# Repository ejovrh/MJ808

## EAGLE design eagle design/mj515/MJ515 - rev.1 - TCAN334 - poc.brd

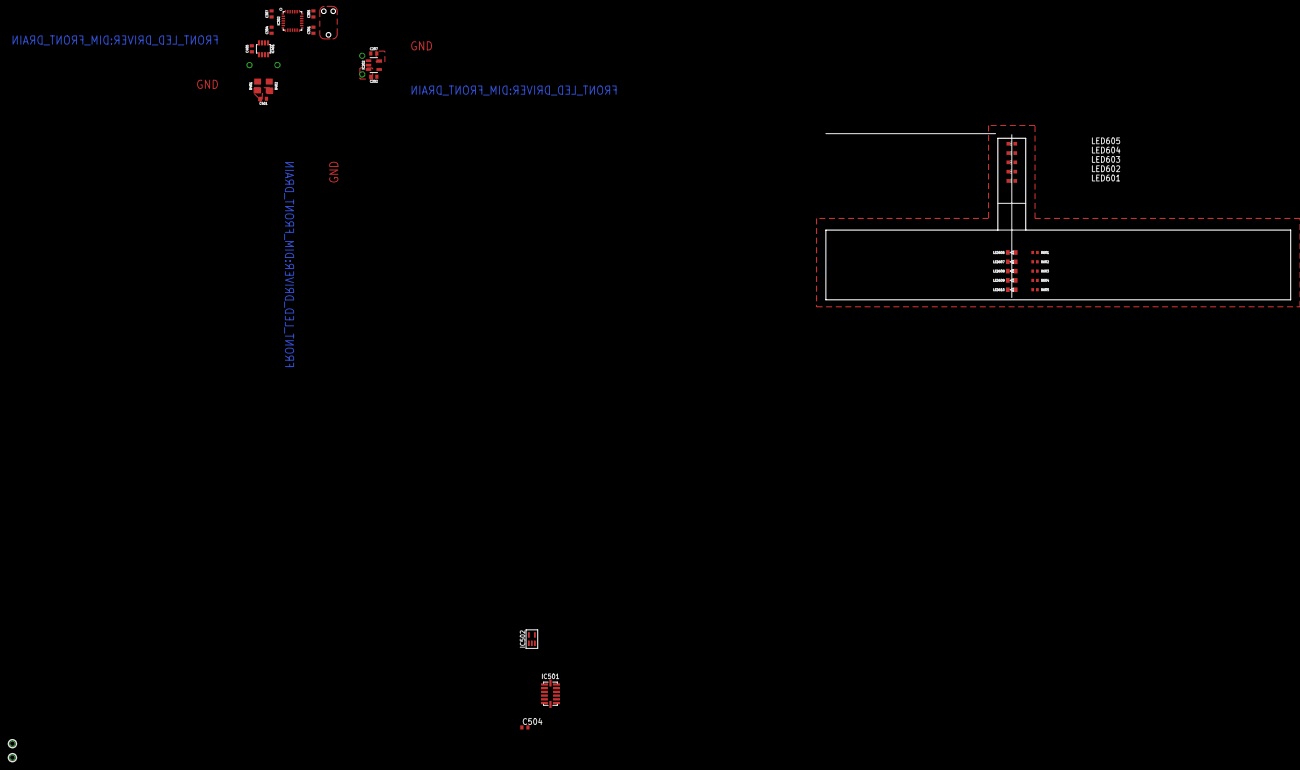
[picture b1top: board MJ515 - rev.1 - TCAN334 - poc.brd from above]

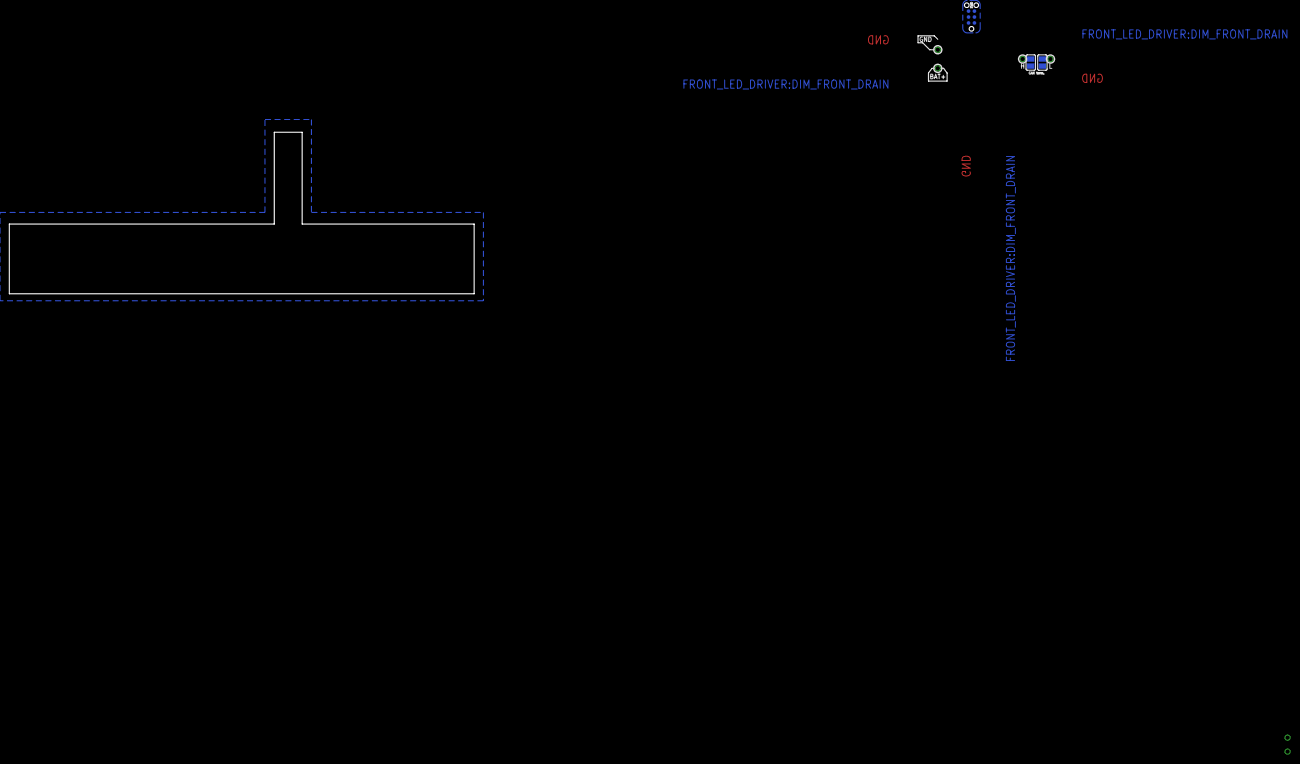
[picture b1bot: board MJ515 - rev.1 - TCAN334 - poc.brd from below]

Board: 2 copper layers, 100.0 x 34.8 mm, 40 parts (7 on the bottom side), 25 nets, no tracks yet.

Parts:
C202, C207, C304: 1uF / 10V; C0402
C301, C305, C307, C405: 0.1uF / 10V; C0402
C401: 47nF / 10V; C0402
C504: 0.1u / 16V; C0402
IC202: LDK320AM33R; SOT-23-5L
IC302: STM32F042G6U6; UFQFPN-28
IC401: TCAN334; SOT23-8
IC501: ADXL345; LGA14
IC502: 74HCT1G32GW; SOT353/5
LED601, LED602, LED603, LED604, LED605: CHIP-LED0603
LED606, LED607, LED608, LED609, LED610: 0603
R401, R402: 60R, 0.5W; R0805
R601, R602, R603, R604, R605: 10k; R0402
SJ401: CAN H term.; SJ
SJ402: CAN L term.; SJ
SWD1: TC2030-NL
TP1: LiIon + Terminal; TH-0.9
TP2: LiIon - Terminal; TH-0.9
TP3, TP5: CAN high; TH-0.9
TP4, TP6: CAN low; TH-0.9

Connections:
3V3: C207.2, C301.2, C304.2, C305.2, C405.1, C504.1, IC202.OUT, IC302.5_VDDA, IC302.17_VDD, IC302.18_VDDIO2, IC401.P$3, IC501.VCC, IC501.VDD, IC502.VCC, LED606.C, LED607.C, LED608.C, LED609.C, LED610.C, SWD1.1_TVCC
!STBY!: IC302.23_PA15, IC401.P$8
ACCELEROMETER:ADXL345SDA: IC501.SDA, IC502.Y
ADXL345_INT1: IC302.6_PA0, IC501.INT1
BAT+: C202.1, IC202.EN, IC202.IN, TP1.P$1
BIT1: IC302.24_PB3, LED607.E, R602.2
BIT2: IC302.25_PB4, LED608.E, R603.2
BIT3: IC302.26_PB5, LED609.E, R604.2
BIT4: IC302.27_PB6, LED610.E, R605.2
CAN_H: IC401.P$7, SJ401.1, TP3.P$1, TP5.P$1
CAN_INFRA:H: R402.2, SJ401.2
CAN_INFRA:L: R401.1, SJ402.2
CAN_INFRA:SPLIT: C401.1, R401.2, R402.1
CAN_L: IC401.P$6, SJ402.1, TP4.P$1, TP6.P$1
CAN_RX: IC302.19_PA9-[PA11], IC401.P$4
CAN_TX: IC302.20_PA10-[PA12], IC401.P$1
CLK: IC302.11_PA5, IC501.SCL
CS: IC302.10_PA4, IC501.!CS!, IC502.A
GND: C202.2, C207.1, C301.1, C304.1, C305.1, C307.1, C401.2, C405.2, C504.2, IC202.GND, IC302.16_VSS, IC401.P$2, IC501.GND1, IC501.GND2, IC501.GND3, IC502.GND, R601.1, R602.1, R603.1, R604.1, R605.1, SWD1.5_GND, TP2.P$1
IDX: IC302.7_PA1, LED606.E, R601.2
MISO: IC302.12_PA6, IC501.SDO
MOSI: IC302.13_PA7, IC502.B
SYS_NRST: C307.2, IC302.4_NRST, SWD1.3_T_NRST
SYS_SWCLK: IC302.22_PA14, SWD1.4_T_SWCLK
SYS_SWDIO: IC302.21_PA13, SWD1.2_T_SWDIO

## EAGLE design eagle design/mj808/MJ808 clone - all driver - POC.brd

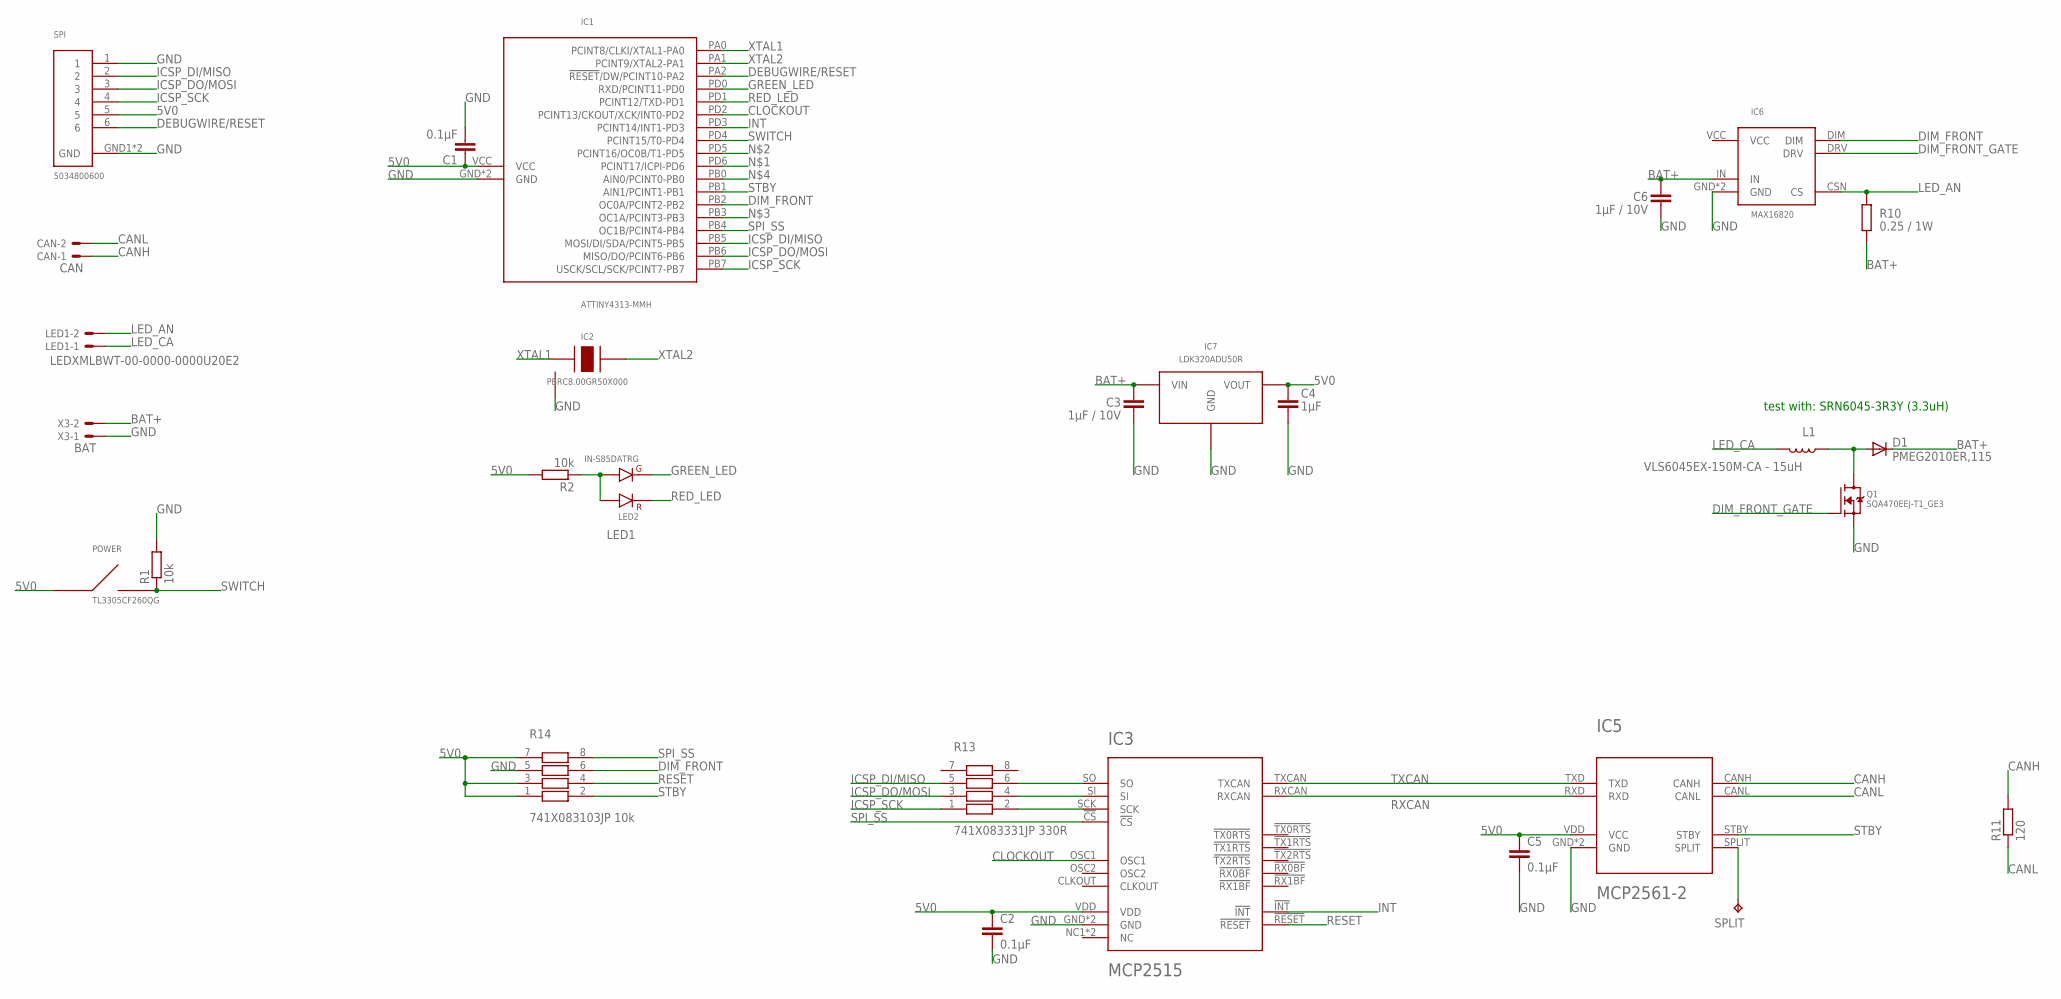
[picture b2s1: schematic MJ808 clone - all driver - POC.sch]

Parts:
C1, C2, C5: 0.1μF; C0402
C3, C6: 1μF / 10V; C0402
C4: 1μF; C0402
CAN: CAN; 22-23-2021
D1: PMEG2010ER,115; SOD123
IC1: ATTINY4313-MMH; VQFN-20
IC2: PBRC8.00GR50X000; SMT
IC3: MCP2515; QFN20
IC5: MCP2561-2; DFN10
IC6: MAX16820; TDFN-6-EP
IC7: LDK320ADU50R; SOT-89
L1: VLS6045EX-150M-CA - 15uH; SRN6045
LED1: LEDXMLBWT-00-0000-0000U20E2; 22-23-2021
LED2: IN-S85DATRG; SMD
POWER: TL3305CF260QG; SMD
Q1: SQA470EEJ-T1_GE3; SC-70-6
R1, R2: 10k; R0402
R10: 0.25 / 1W; R1210
R11: 120; R0805
R13: 741X083331JP 330R; 0402
R14: 741X083103JP 10k; 0402
SPI: 5034800600; SMT
SPLIT: TPB2,54; B2,54
X3: BAT; 22-23-2021

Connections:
5V0: C1.1, C2.1, C4.2, C5.1, IC1.VCC, IC3.VDD, IC5.VDD (VCC), IC7.VOUT, POWER.1, POWER.2, R2.2, R14.1, R14.3, R14.7, SPI.5
BAT+: C3.1, C6.1, D1.C, IC6.IN, IC7.VIN, R10.2, X3.2
CANH: CAN.1, IC5.CANH, R11.2
CANL: CAN.2, IC5.CANL, R11.1
CLOCKOUT: IC1.PD2 (PCINT13/CKOUT/XCK/INT0-PD2), IC3.OSC1
DEBUGWIRE/RESET: IC1.PA2 (!RESET!/DW/PCINT10-PA2), SPI.6
DIM_BRAKE_DRAIN: D1.A, L1.1, Q1.D
DIM_FRONT: IC1.PB2 (OC0A/PCINT2-PB2), IC6.DIM, R14.6
DIM_FRONT_GATE: IC6.DRV, Q1.G
GND: C1.2, C2.2, C3.2, C4.1, C5.2, C6.2, IC1.GND, IC1.GND1 (GND), IC2.GND, IC3.GND, IC3.GND6 (GND), IC5.GND, IC5.VSS (GND), IC6.GND, IC6.GND1 (GND), IC7.GND, Q1.S, R1.2, R14.5, SPI.1, SPI.GND1 (GND), SPI.GND2 (GND), X3.1
GREEN_LED: IC1.PD0 (RXD/PCINT11-PD0), LED2.3
ICSP_DI/MISO: IC1.PB5 (MOSI/DI/SDA/PCINT5-PB5), R13.5, SPI.2
ICSP_DO/MOSI: IC1.PB6 (MISO/DO/PCINT6-PB6), R13.3, SPI.3
ICSP_SCK: IC1.PB7 (USCK/SCL/SCK/PCINT7-PB7), R13.1, SPI.4
INT: IC1.PD3 (PCINT14/INT1-PD3), IC3.!INT!
LED1: LED2.1, LED2.4, R2.1
LED_AN: IC6.CSN (CS), LED1.2, R10.1
LED_CA: L1.2, LED1.1
RED_LED: IC1.PD1 (PCINT12/TXD-PD1), LED2.2
RESET: IC3.!RESET!, R14.4
RXCAN: IC3.RXCAN, IC5.RXD
SPI_MISO: IC3.SO, R13.6
SPI_MOSI: IC3.SI, R13.4
SPI_SCK: IC3.SCK, R13.2
SPI_SS: IC1.PB4 (OC1B/PCINT4-PB4), IC3.!CS!, R14.8
SPLIT: IC5.SPLIT, SPLIT.TP
STBY: IC1.PB1 (AIN1/PCINT1-PB1), IC5.STBY, R14.2
SWITCH: IC1.PD4 (PCINT15/T0-PD4), POWER.3, POWER.4, R1.1
TXCAN: IC3.TXCAN, IC5.TXD
VCC: IC6.VCC
XTAL1: IC1.PA0 (PCINT8/CLKI/XTAL1-PA0), IC2.XTAL1
XTAL2: IC1.PA1 (PCINT9/XTAL2-PA1), IC2.XTAL2

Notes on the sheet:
test with: SRN6045-3R3Y (3.3uH)

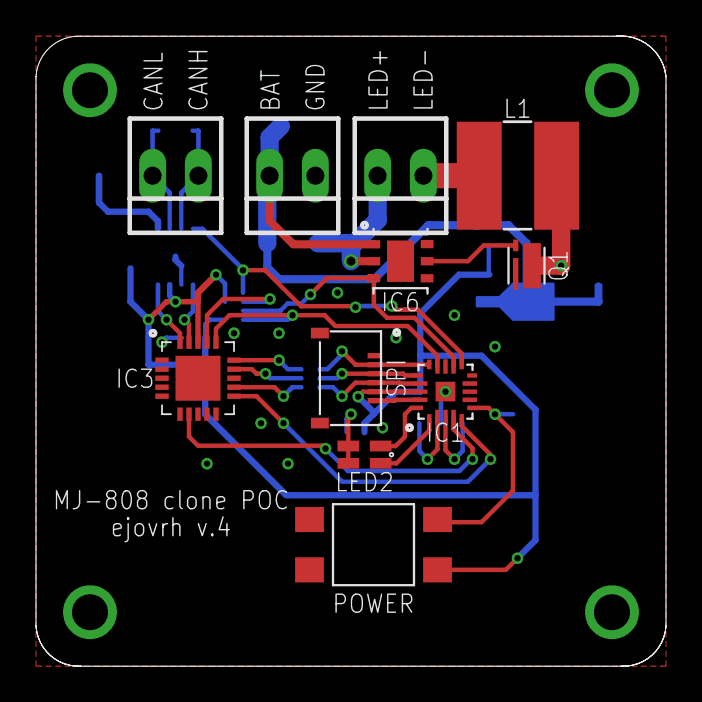
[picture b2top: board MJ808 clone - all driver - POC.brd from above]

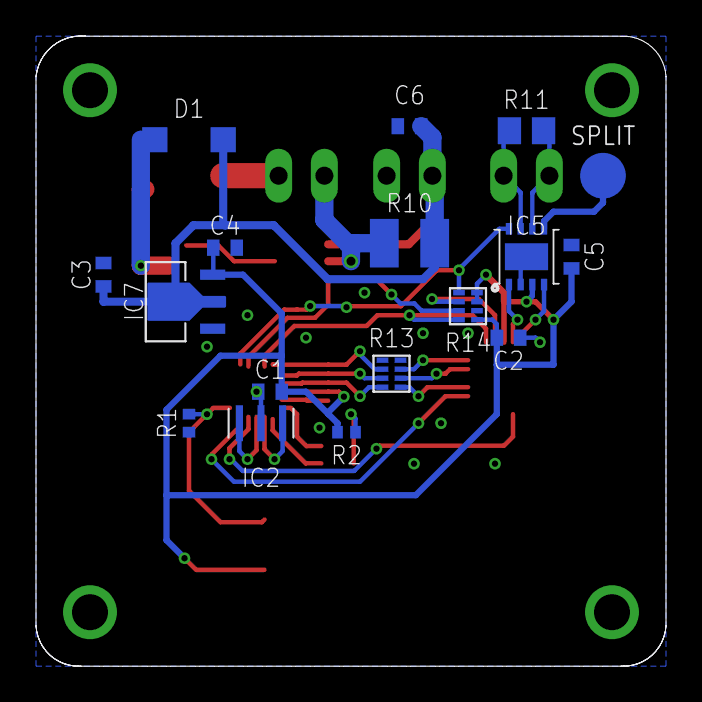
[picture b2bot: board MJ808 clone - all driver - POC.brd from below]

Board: 2 copper layers, 35.0 x 35.0 mm, 28 parts (17 on the bottom side), 31 nets.

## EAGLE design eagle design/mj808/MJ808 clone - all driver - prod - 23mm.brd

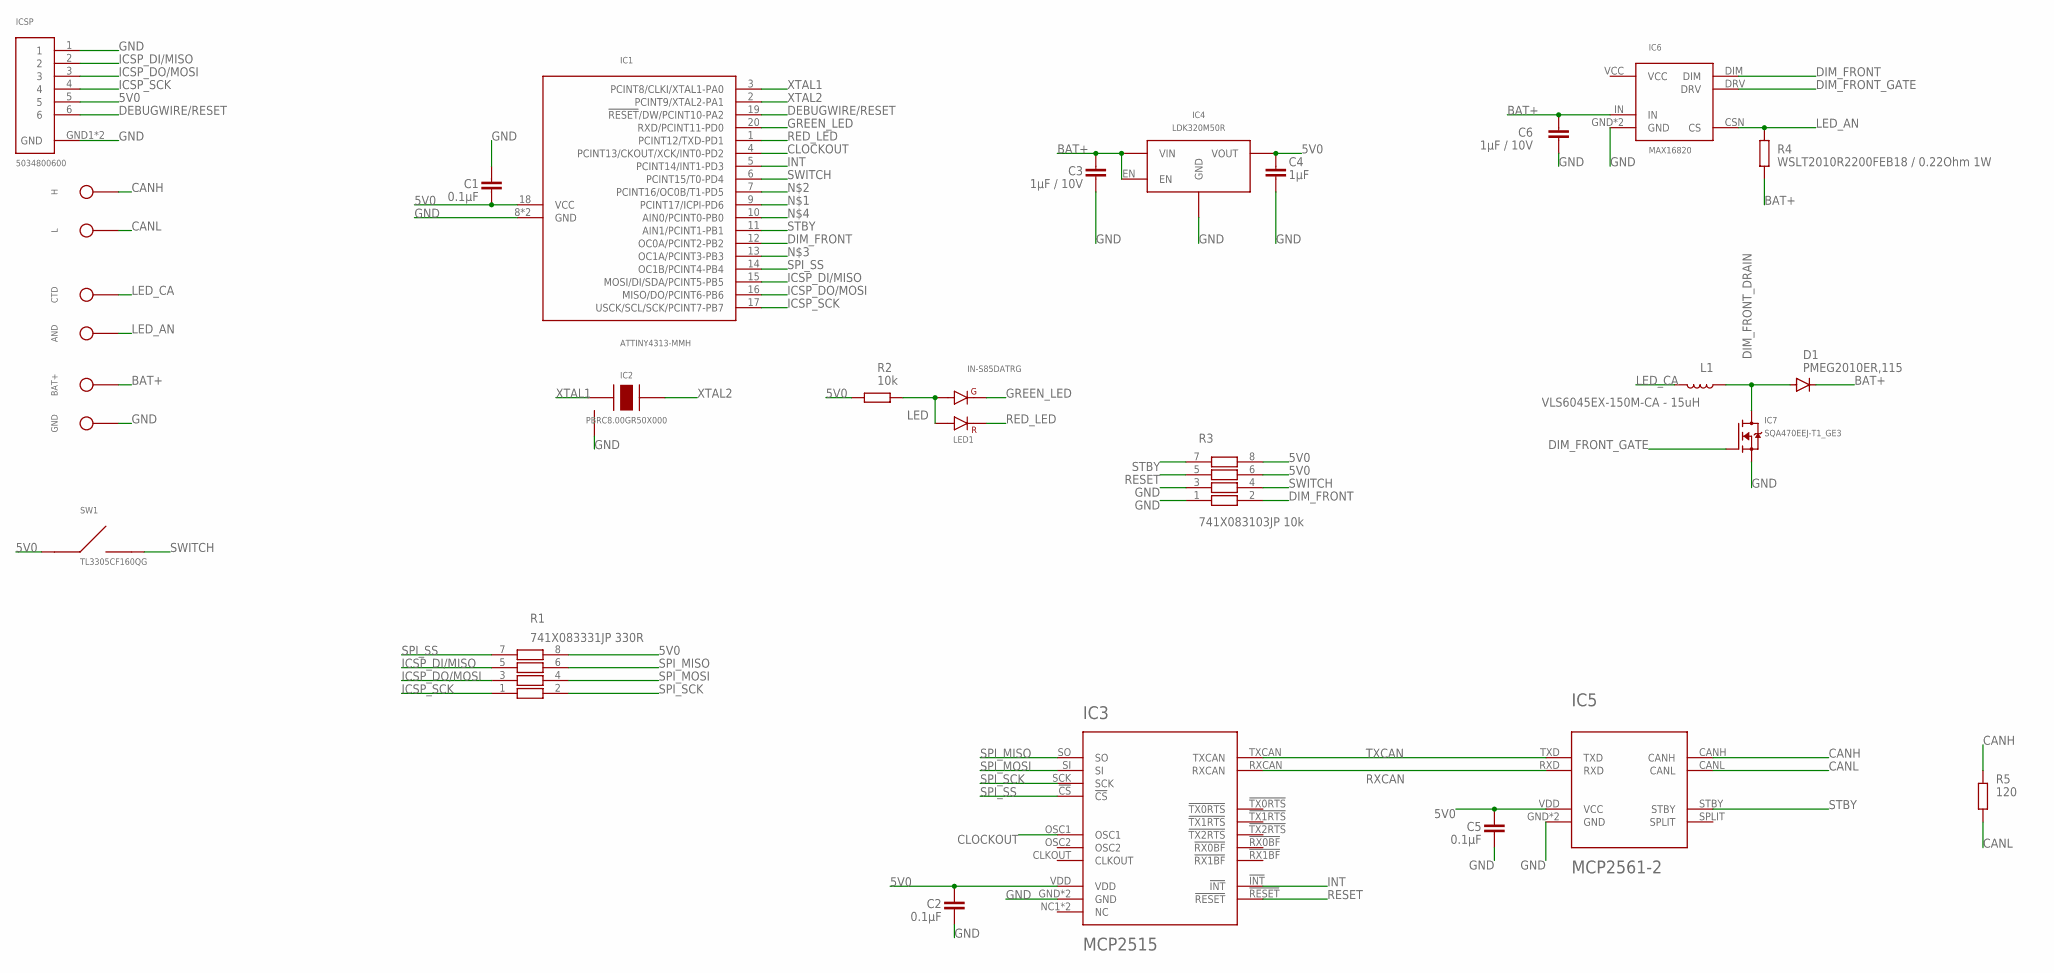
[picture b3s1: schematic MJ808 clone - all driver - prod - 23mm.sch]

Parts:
AND: LED anode; TH-1.2MM
BAT+: LiIon + Terminal; TH-1.2MM
C1, C2, C5: 0.1μF; C0402
C3, C6: 1μF / 10V; C0402
C4: 1μF; C0402
CTD: LED cathode; TH-1.2MM
D1: PMEG2010ER,115; SOD123
GND: LiIon - Terminal; TH-1.2MM
H: CAN high; TH-1.2MM
IC1: ATTINY4313-MMH; VQFN-20
IC2: PBRC8.00GR50X000; SMT
IC3: MCP2515; QFN20
IC4: LDK320M50R; SOT-23-5L
IC5: MCP2561-2; DFN10
IC6: MAX16820; TDFN-6-EP
IC7: SQA470EEJ-T1_GE3; SC-70-6
ICSP: 5034800600; SMT
L: CAN low; TH-1.2MM
L1: VLS6045EX-150M-CA - 15uH; SRN6045
LED1: IN-S85DATRG; SMD
R1: 741X083331JP 330R; 0402-4R
R2: 10k; R0402
R3: 741X083103JP 10k; 0402-4R
R4: WSLT2010R2200FEB18 / 0.22Ohm 1W; R2010
R5: 120; R0805
SW1: TL3305CF160QG; SMD

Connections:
5V0: C1.1, C2.1, C4.2, C5.1, IC1.18 (VCC), IC3.VDD, IC4.OUT (VOUT), IC5.VDD (VCC), ICSP.5, R1.8, R2.2, R3.6, R3.8, SW1.1, SW1.2
BAT+: BAT+.TP$1, C3.1, C6.1, D1.C, IC4.EN, IC4.IN (VIN), IC6.IN, R4.2
CANH: H.TP$1, IC5.CANH, R5.2
CANL: IC5.CANL, L.TP$1, R5.1
CLOCKOUT: IC1.4 (PCINT13/CKOUT/XCK/INT0-PD2), IC3.OSC1
DEBUGWIRE/RESET: IC1.19 (!RESET!/DW/PCINT10-PA2), ICSP.6
DIM_FRONT: IC1.12 (OC0A/PCINT2-PB2), IC6.DIM, R3.2
DIM_FRONT_DRAIN: D1.A, IC7.1D (D), IC7.2D (D), IC7.5D (D), IC7.6D (D), IC7.D, L1.1
DIM_FRONT_GATE: IC6.DRV, IC7.3G (G)
GND: C1.2, C2.2, C3.2, C4.1, C5.2, C6.2, GND.TP$1, IC1.8 (GND), IC1.GND, IC2.GND, IC3.GND, IC3.GND6 (GND), IC4.GND, IC5.GND, IC5.VSS (GND), IC6.GND, IC6.GND1 (GND), IC7.4S (S), IC7.S, ICSP.1, ICSP.GND1 (GND), ICSP.GND2 (GND), R3.1, R3.3
GREEN_LED: IC1.20 (RXD/PCINT11-PD0), LED1.3
ICSP_DI/MISO: IC1.15 (MOSI/DI/SDA/PCINT5-PB5), ICSP.2, R1.5
ICSP_DO/MOSI: IC1.16 (MISO/DO/PCINT6-PB6), ICSP.3, R1.3
ICSP_SCK: IC1.17 (USCK/SCL/SCK/PCINT7-PB7), ICSP.4, R1.1
INT: IC1.5 (PCINT14/INT1-PD3), IC3.!INT!
LED: LED1.1, LED1.4, R2.1
LED_AN: AND.TP$1, IC6.CSN (CS), R4.1
LED_CA: CTD.TP$1, L1.2
unnamed: IC1.3 (PCINT8/CLKI/XTAL1-PA0), IC2.XTAL1
unnamed: IC1.2 (PCINT9/XTAL2-PA1), IC2.XTAL2
RED_LED: IC1.1 (PCINT12/TXD-PD1), LED1.2
RESET: IC3.!RESET!, R3.5
RXCAN: IC3.RXCAN, IC5.RXD
SPI_MISO: IC3.SO, R1.6
SPI_MOSI: IC3.SI, R1.4
SPI_SCK: IC3.SCK, R1.2
SPI_SS: IC1.14 (OC1B/PCINT4-PB4), IC3.!CS!, R1.7
STBY: IC1.11 (AIN1/PCINT1-PB1), IC5.STBY, R3.7
SWITCH: IC1.6 (PCINT15/T0-PD4), R3.4, SW1.3, SW1.4
TXCAN: IC3.TXCAN, IC5.TXD
VCC: IC6.VCC

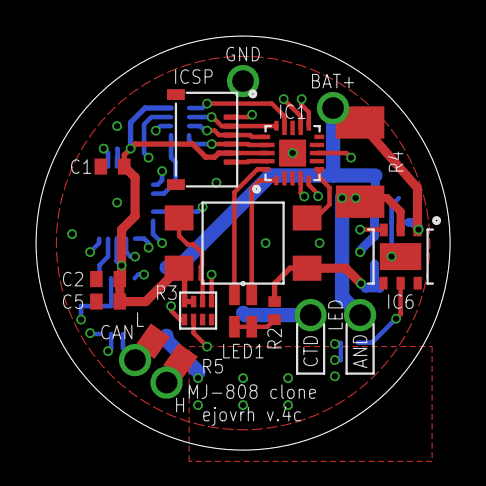
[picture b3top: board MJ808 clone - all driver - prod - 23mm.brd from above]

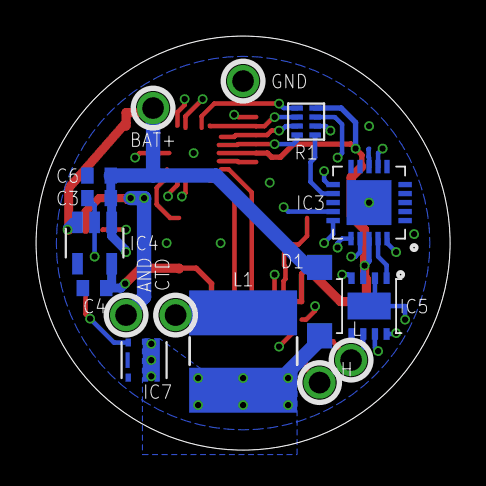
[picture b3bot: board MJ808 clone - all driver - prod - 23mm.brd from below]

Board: 4 copper layers, 23.0 x 23.0 mm, 28 parts (16 on the bottom side), 28 nets.

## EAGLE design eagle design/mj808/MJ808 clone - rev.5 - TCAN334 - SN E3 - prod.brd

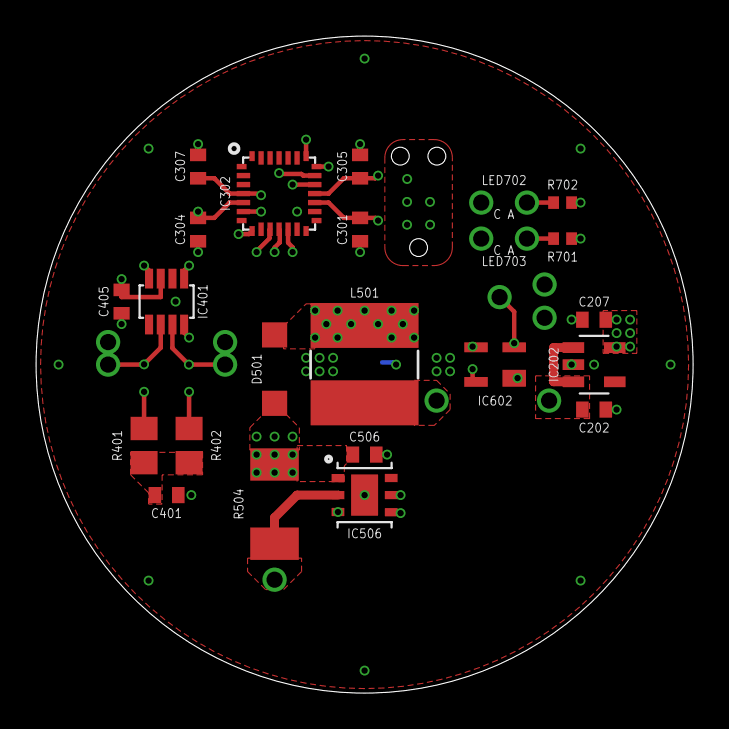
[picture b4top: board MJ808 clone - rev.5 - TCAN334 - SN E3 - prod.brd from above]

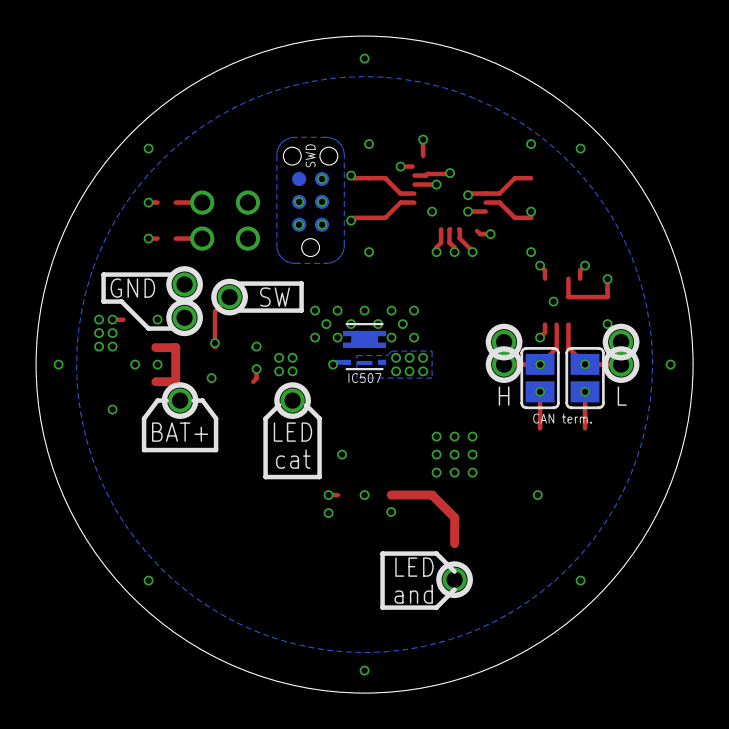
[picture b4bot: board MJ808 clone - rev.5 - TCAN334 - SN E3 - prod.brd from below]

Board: 4 copper layers, 36.5 x 36.5 mm, 37 parts (14 on the bottom side), 25 nets.

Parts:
C202, C207, C304, C506: 1uF / 10V; C0402
C301, C305, C307, C405: 0.1uF / 10V; C0402
C401: 47nF / 10V; C0402
D501: PMEG2010ER,115; SOD123
IC202: LDK320AM33R; SOT-23-5L
IC302: STM32F042G6U6; UFQFPN-28
IC401: TCAN334; SOT23-8
IC506: MAX16820; TDFN-6-EP
IC507: SQA470EEJ-T1_GE3; SC-70-6
IC602: MAX6816EUS+T; 4SOT143
L501: VLS6045EX-150M-CA - 15uH; SRN6045
LED702: WP7113VRVC1C; TH
LED703: LTL2R3TGY3KS; TH
R401, R402: 60R, 0.5W; R0805
R504: 0.18R; R2010
R701, R702: 0R, >120mW; R0402
SJ401: CAN H term.; SJ
SJ402: CAN L term.; SJ
SWD1: TC2030-NL
TP1: LiIon + Terminal; TH-0.9
TP2: LiIon - Terminal; TH-0.9
TP3, TP601, TP602: LED anode; TH-0.9
TP4: LED cathode; TH-0.9
TP5, TP7: CAN high; TH-0.9
TP6, TP8: CAN low; TH-0.9

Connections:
3V3: C207.2, C301.2, C304.2, C305.2, C405.1, IC202.OUT, IC302.5_VDDA, IC302.17_VDD, IC302.18_VDDIO2, IC401.P$3, IC602.4_VCC, R701.1, R702.1, SWD1.1_TVCC
!STBY!: IC302.11_PA5, IC401.P$8
BAT+: C202.1, C506.1, D501.C, IC202.EN, IC202.IN, IC506.IN, R504.2, TP1.P$1
CAN_H: IC401.P$7, SJ401.1, TP5.P$1, TP7.P$1
CAN_INFRA:H: R402.2, SJ401.2
CAN_INFRA:L: R401.1, SJ402.2
CAN_INFRA:SPLIT: C401.1, R401.2, R402.1
CAN_L: IC401.P$6, SJ402.1, TP6.P$1, TP8.P$1
CAN_RX: IC302.19_PA9-[PA11], IC401.P$4
CAN_TX: IC302.20_PA10-[PA12], IC401.P$1
DIM_FRONT: IC302.12_PA6, IC506.DIM
FRONT_LED_DRIVER:DIM_FRONT_DRAIN: D501.A, IC507.1D, IC507.2D, IC507.5D, IC507.6D, IC507.D, L501.1
FRONT_LED_DRIVER:DIM_FRONT_GATE: IC506.DRV, IC507.3G
GND: C202.2, C207.1, C301.1, C304.1, C305.1, C307.1, C401.2, C405.2, C506.2, IC202.GND, IC302.16_VSS, IC401.P$2, IC506.GND, IC506.GND1, IC507.4S, IC507.S, IC602.1_GND, SWD1.5_GND, TP2.P$1, TP602.P$1
GREEN: IC302.10_PA4, LED703.CAT
LED_AN: IC506.CSN, R504.1, TP3.P$1
LED_CA: L501.2, TP4.P$1
PUSHBUTTON:SWITCH_IN: IC602.2_IN, TP601.P$1
RED: IC302.8_PA2, LED702.CAT
SWITCH: IC302.6_PA0, IC602.3_OUT
SYS_NRST: C307.2, IC302.4_NRST, SWD1.3_T_NRST
SYS_SWCLK: IC302.22_PA14, SWD1.4_T_SWCLK
SYS_SWDIO: IC302.21_PA13, SWD1.2_T_SWDIO
USER_LED:GREEN_AND: LED703.AND, R701.2
USER_LED:RED_AND: LED702.AND, R702.2

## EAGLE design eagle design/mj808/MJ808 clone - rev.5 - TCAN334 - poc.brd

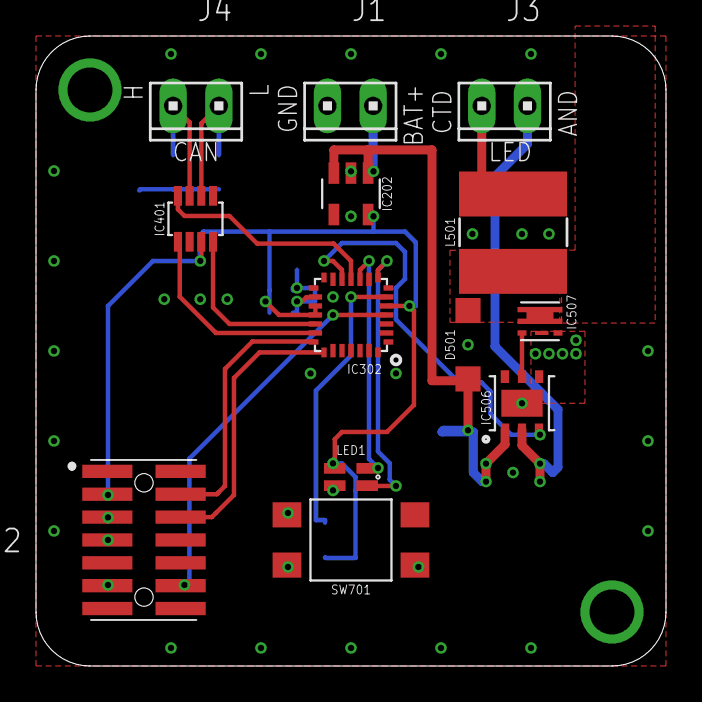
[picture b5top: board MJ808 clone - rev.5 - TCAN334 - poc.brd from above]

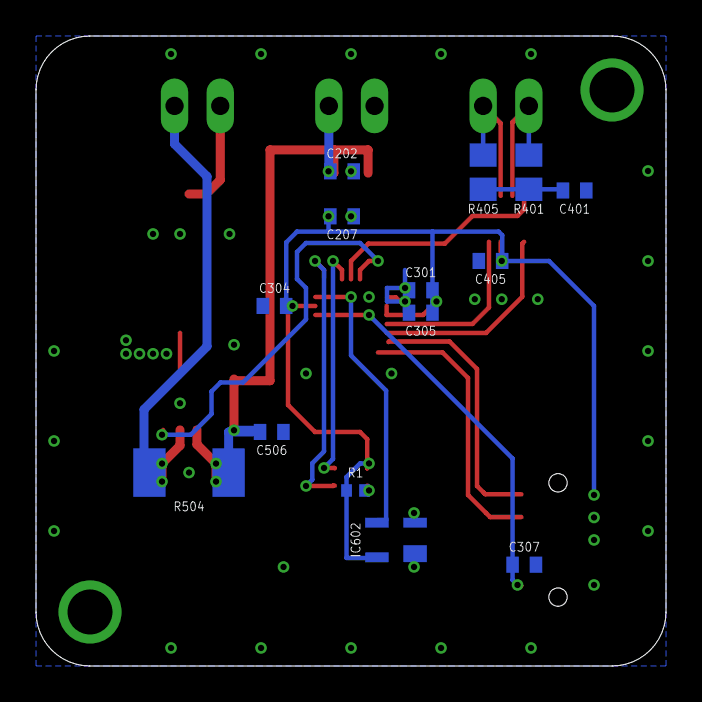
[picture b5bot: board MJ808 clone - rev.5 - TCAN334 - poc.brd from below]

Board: 2 copper layers, 35.0 x 35.0 mm, 27 parts (14 on the bottom side), 22 nets.

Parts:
C202, C207, C304, C506: 1uF / 10V; C0402
C301, C305, C307, C405: 0.1uF / 10V; C0402
C401: 47nF / 10V; C0402
D501: PMEG2010ER,115; SOD123
IC202: LDK320AM33R; SOT-23-5L
IC302: STM32F042G6U6; UFQFPN-28
IC401: TCAN334; SOT23-8
IC506: MAX16820; TDFN-6-EP
IC507: SQA470EEJ-T1_GE3; SC-70-6
IC602: MAX6816EUS+T; 4SOT143
J1: Power Supply; 10X02MTA
J2: FTSH-107-01-L-DV-K-A; FTSH10701LDVKA
J3: LED; 10X02MTA
J4: CAN; 10X02MTA
L501: VLS6045EX-150M-CA - 15uH; SRN6045
LED1: APHBM2012SURKZGKC; SMD
R1: 68R; R0402
R401, R405: 60; R0805
R504: WSLT2010R2200FEB18 / 0.22Ohm 1W; R2010
SW701: TL3305CF160QG; SMD

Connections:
3V3: C207.2, C301.2, C304.2, C305.2, C405.1, IC202.OUT, IC302.5_VDDA, IC302.17_VDD, IC302.18_VDDIO2, IC401.P$3, IC602.4_VCC, J2.3, LED1.4, R1.1
!STBY!: IC302.11_PA5, IC401.P$8
BAT+: C202.1, C506.1, D501.C, IC202.EN, IC202.IN, IC506.IN, J1.2, R504.2
CAN_H: IC401.P$7, J4.1, R401.2
CAN_INFRA:SPLIT: C401.1, R401.1, R405.2
CAN_L: IC401.P$6, J4.2, R405.1
CAN_RX: IC302.19_PA9-[PA11], IC401.P$4
CAN_TX: IC302.20_PA10-[PA12], IC401.P$1
DIM_FRONT: IC302.12_PA6, IC506.DIM
FRONT_LED_DRIVER:DIM_FRONT_DRAIN: D501.A, IC507.1D, IC507.2D, IC507.5D, IC507.6D, IC507.D, L501.1
FRONT_LED_DRIVER:DIM_FRONT_GATE: IC506.DRV, IC507.3G
GND: C202.2, C207.1, C301.1, C304.1, C305.1, C307.1, C401.2, C405.2, C506.2, IC202.GND, IC302.16_VSS, IC401.P$2, IC506.GND, IC506.GND1, IC507.4S, IC507.S, IC602.1_GND, J1.1, J2.5, J2.7, J2.11, SW701.3, SW701.4
GREEN_LED: IC302.10_PA4, LED1.3
LED_AN: IC506.CSN, J3.2, R504.1
LED_CA: J3.1, L501.2
PUSHBUTTON:SWITCH_IN: IC602.2_IN, SW701.1, SW701.2
RED_LED: IC302.8_PA2, LED1.2
SWITCH: IC302.6_PA0, IC602.3_OUT
SYS_NRST: C307.2, IC302.4_NRST, J2.12
SYS_SWCLK: IC302.22_PA14, J2.6
SYS_SWDIO: IC302.21_PA13, J2.4
USER-LED-CTD: LED1.1, R1.2

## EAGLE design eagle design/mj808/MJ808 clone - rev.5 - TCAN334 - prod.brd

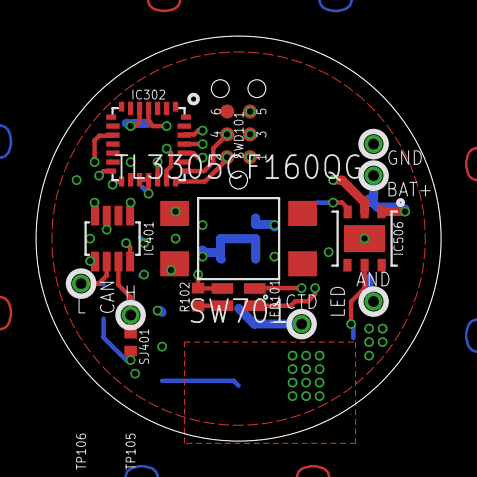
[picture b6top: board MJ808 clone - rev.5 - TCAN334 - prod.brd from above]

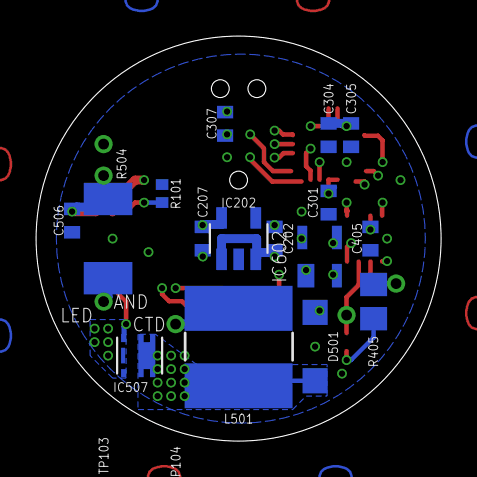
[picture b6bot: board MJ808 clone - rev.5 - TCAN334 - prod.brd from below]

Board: 4 copper layers, 22.5 x 22.5 mm, 30 parts (16 on the bottom side), 23 nets.

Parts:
C202, C506: 1μF / 10V; C0402
C207: 1μF; C0402
C301, C305, C307: 0.1u; C0402
C304: 1u; C0402
C405: 0.1μF; C0402
D501: PMEG2010ER,115; SOD123
IC202: LDK320AM33R; SOT-23-5L
IC302: STM32F042G6U6; UFQFPN-28
IC401: TCAN334; SOT23-8
IC506: MAX16820; TDFN-6-EP
IC507: SQA470EEJ-T1_GE3; SC-70-6
IC602: MAX6816EUS+T; 4SOT143
L501: VLS6045EX-150M-CA - 15uH; SRN6045
LED101: APHBM2012SURKZGKC; SMD
R101: 10k; R0402
R102: 68R; R0402
R405: 120; R0805
R504: WSLT2010R2200FEB18 / 0.22Ohm 1W; R2010
SJ401: CAN termination; R0402
SW701: TL3305CF160QG; SMD
SWD101: TC2030-NL
TP101: LiIon + Terminal; TH
TP102: LiIon - Terminal; TH
TP103: LED anode; TH
TP104: LED cathode; TH
TP105: CAN high; TH
TP106: CAN low; TH

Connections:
3V3: C207.2, C301.2, C304.2, C305.2, C405.1, IC202.OUT, IC302.5_VDDA, IC302.17_VDD, IC302.18_VDDIO2, IC401.P$3, IC602.4_VCC, LED101.4, R102.1, SWD101.1_TVCC
!SHDN!: IC302.10_PA4, IC401.P$5
!STBY!: IC302.15_PB1, IC401.P$8
BAT+: C202.1, C506.1, D501.C, IC202.EN, IC202.IN, IC506.IN, R504.2, TP101.TP$1
CAN_H: IC401.P$7, SJ401.2, TP105.TP$1
CAN_INFRA:CAN_JMPR: R405.2, SJ401.1
CAN_L: IC401.P$6, R405.1, TP106.TP$1
CAN_RX: IC302.19_PA9-[PA11], IC401.P$4
CAN_TX: IC302.20_PA10-[PA12], IC401.P$1
DIM_FRONT: IC302.24_PB3, IC506.DIM, R101.2
FRONT_LED_DRIVER:DIM_FRONT_DRAIN: D501.A, IC507.1D, IC507.2D, IC507.5D, IC507.6D, IC507.D, L501.1
FRONT_LED_DRIVER:DIM_FRONT_GATE: IC506.DRV, IC507.3G
GND: C202.2, C207.1, C301.1, C304.1, C305.1, C307.1, C405.2, C506.2, IC202.GND, IC302.16_VSS, IC401.P$2, IC506.GND, IC506.GND1, IC507.4S, IC507.S, IC602.1_GND, R101.1, SW701.3, SW701.4, SWD101.5_GND, TP102.TP$1
GREEN_LED: IC302.26_PB5, LED101.3
LED_AN: IC506.CSN, R504.1, TP103.TP$1
LED_CA: L501.2, TP104.TP$1
PUSHBUTTON:SWITCH_IN: IC602.2_IN, SW701.1, SW701.2
RED_LED: IC302.25_PB4, LED101.2
SWITCH: IC302.14_PB0, IC602.3_OUT
SYS_NRST: C307.2, IC302.4_NRST, SWD101.3_T_NRST
SYS_SWCLK: IC302.22_PA14, SWD101.4_T_SWCLK
SYS_SWDIO: IC302.21_PA13, SWD101.2_T_SWDIO
USER-LED-CTD: LED101.1, R102.2

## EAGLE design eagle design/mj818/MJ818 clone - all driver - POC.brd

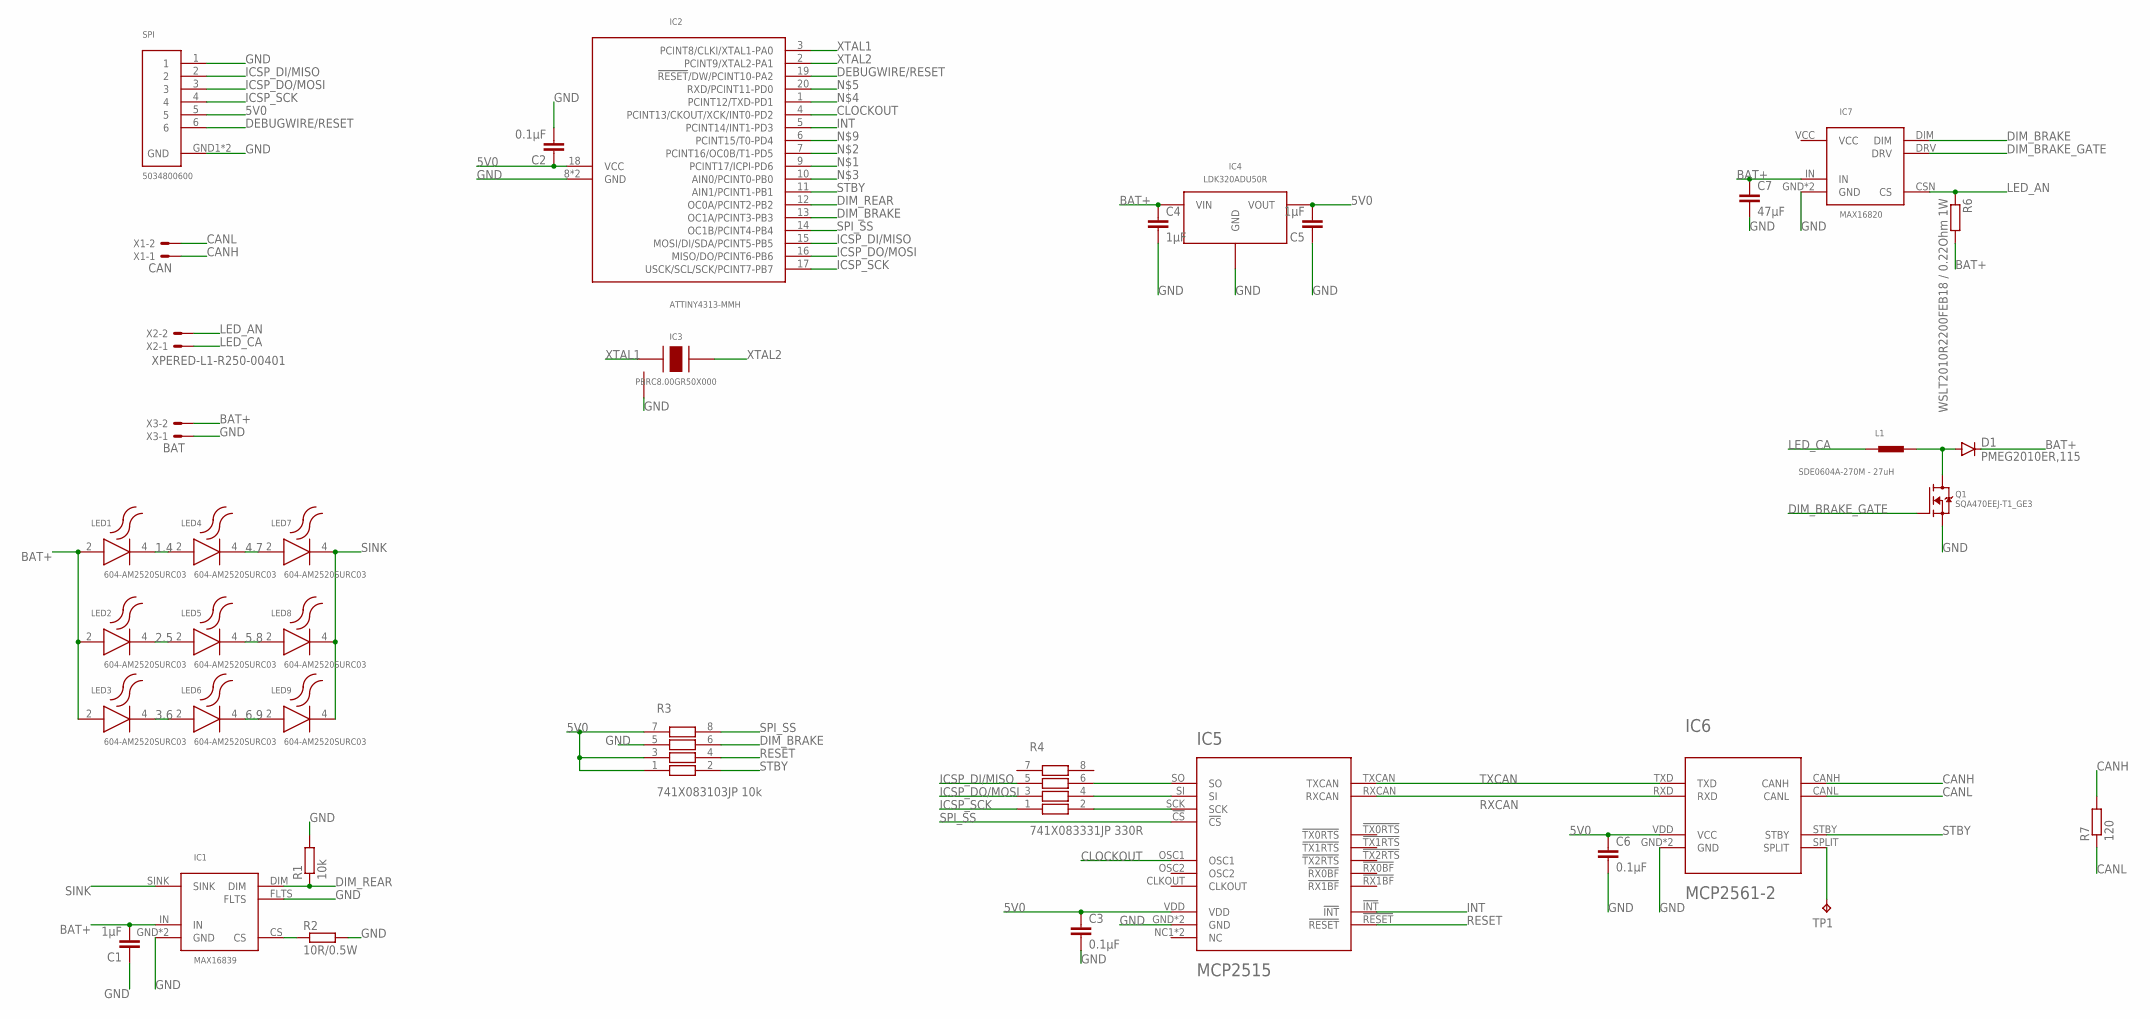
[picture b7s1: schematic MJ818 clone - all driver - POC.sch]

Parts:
C1, C4, C5: 1μF; C0402
C2, C3, C6: 0.1μF; C0402
C7: 47μF; C0805
D1: PMEG2010ER,115; SOD123
IC1: MAX16839; TDFN-6-EP
IC2: ATTINY4313-MMH; VQFN-20
IC3: PBRC8.00GR50X000; SMT
IC4: LDK320ADU50R; SOT-89-D
IC5: MCP2515; QFN20
IC6: MCP2561-2; DFN10
IC7: MAX16820; TDFN-6-EP
L1: SDE0604A-270M - 27uH; SMT
LED1, LED2, LED3, LED4, LED5, LED6, LED7, LED8, LED9: 604-AM2520SURC03; SMD
Q1: SQA470EEJ-T1_GE3; SC-70-6
R1: 10k; R0402
R2: 10R/0.5W; R0603
R3: 741X083103JP 10k; 0402
R4: 741X083331JP 330R; 0402
R6: WSLT2010R2200FEB18 / 0.22Ohm 1W; R2010
R7: 120; R0805
SPI: 5034800600; SMT
TP1: TPB2,54; B2,54
X1: CAN; 22-23-2021
X2: XPERED-L1-R250-00401; 22-23-2021
X3: BAT; 22-23-2021

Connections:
1.4: LED1.4 (C), LED4.2 (A)
2.5: LED2.4 (C), LED5.2 (A)
3.6: LED3.4 (C), LED6.2 (A)
4.7: LED4.4 (C), LED7.2 (A)
5.8: LED5.4 (C), LED8.2 (A)
5V0: C2.1, C3.1, C5.2, C6.1, IC2.18 (VCC), IC4.VOUT, IC5.VDD, IC6.VDD (VCC), R3.1, R3.3, R3.7, SPI.5
6.9: LED6.4 (C), LED9.2 (A)
BAT+: C1.2, C4.1, C7.1, D1.C, IC1.IN, IC4.VIN, IC7.IN, LED1.2 (A), LED2.2 (A), LED3.2 (A), R6.2, X3.2
CANH: IC6.CANH, R7.2, X1.1
CANL: IC6.CANL, R7.1, X1.2
CLOCKOUT: IC2.4 (PCINT13/CKOUT/XCK/INT0-PD2), IC5.OSC1
CS: IC1.CS, R2.1
DEBUGWIRE/RESET: IC2.19 (!RESET!/DW/PCINT10-PA2), SPI.6
DIM_BRAKE: IC2.13 (OC1A/PCINT3-PB3), IC7.DIM, R3.6
DIM_BRAKE_DRAIN: D1.A, L1.P$2, Q1.D
DIM_BRAKE_GATE: IC7.DRV, Q1.G
DIM_REAR: IC1.DIM, IC2.12 (OC0A/PCINT2-PB2), R1.1
GND: C1.1, C2.2, C3.2, C4.2, C5.1, C6.2, C7.2, IC1.FLTS, IC1.GND, IC1.GND1 (GND), IC2.8 (GND), IC2.GND, IC3.GND, IC4.GND, IC5.GND, IC5.GND6 (GND), IC6.GND, IC6.VSS (GND), IC7.GND, IC7.GND1 (GND), Q1.S, R1.2, R2.2, R3.5, SPI.1, SPI.GND1 (GND), SPI.GND2 (GND), X3.1
ICSP_DI/MISO: IC2.15 (MOSI/DI/SDA/PCINT5-PB5), R4.5, SPI.2
ICSP_DO/MOSI: IC2.16 (MISO/DO/PCINT6-PB6), R4.3, SPI.3
ICSP_SCK: IC2.17 (USCK/SCL/SCK/PCINT7-PB7), R4.1, SPI.4
INT: IC2.5 (PCINT14/INT1-PD3), IC5.!INT!
LED_AN: IC7.CSN (CS), R6.1, X2.2
LED_CA: L1.P$1, X2.1
RESET: IC5.!RESET!, R3.4
RXCAN: IC5.RXCAN, IC6.RXD
SINK: IC1.SINK, LED7.4 (C), LED8.4 (C), LED9.4 (C)
SPI_MISO: IC5.SO, R4.6
SPI_MOSI: IC5.SI, R4.4
SPI_SCK: IC5.SCK, R4.2
SPI_SS: IC2.14 (OC1B/PCINT4-PB4), IC5.!CS!, R3.8
SPLIT: IC6.SPLIT, TP1.TP
STBY: IC2.11 (AIN1/PCINT1-PB1), IC6.STBY, R3.2
TXCAN: IC5.TXCAN, IC6.TXD
VCC: IC7.VCC
XTAL1: IC2.3 (PCINT8/CLKI/XTAL1-PA0), IC3.XTAL1
XTAL2: IC2.2 (PCINT9/XTAL2-PA1), IC3.XTAL2

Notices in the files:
parts and their libraries:
tag-connect: ©2009 ROFA.cz - modified and updated by Robert Darlington ‹rdarlington@gmail.com›
SparkFun-Coils: Licensing: Creative Commons ShareAlike 4.0 International - https://creativecommons.org/licenses/by-sa/4.0
